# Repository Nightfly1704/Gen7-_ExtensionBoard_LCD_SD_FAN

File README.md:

Gen7-_ExtensionBoard_LCD_SD_FAN
==============================

Extension Board for Gen7 Electronics Version 1.4.1/1.5

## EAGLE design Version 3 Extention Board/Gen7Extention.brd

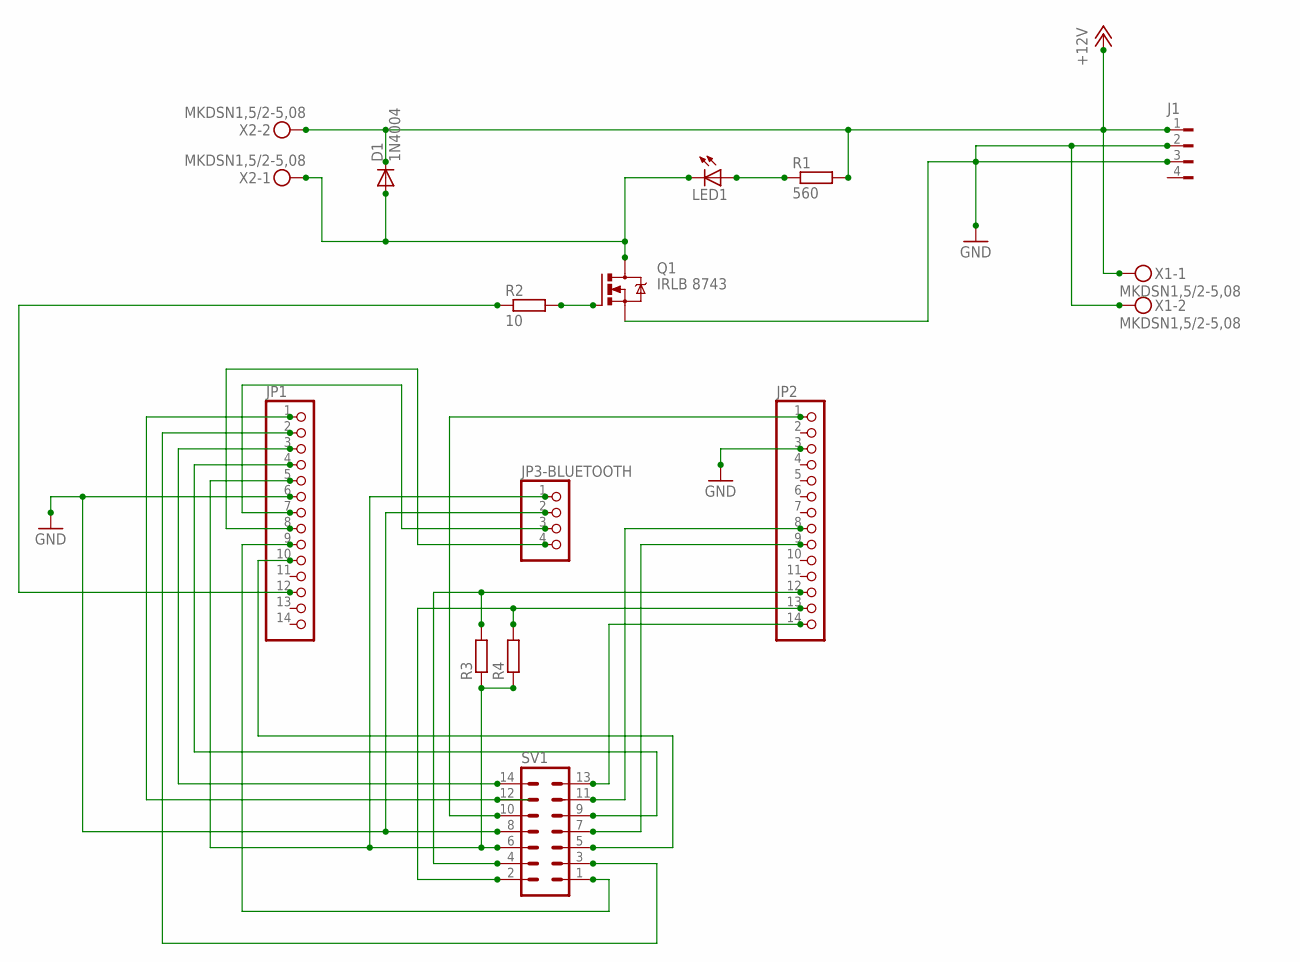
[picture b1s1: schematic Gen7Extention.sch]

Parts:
D1: 1N4004; DO41-10
J1: FLOPPY-4
JP1, JP2: PINHD-1X14; 1X14
JP3-BLUETOOTH: PINHD-1X4; 1X04
LED1: LED3MM
Q1: IRLB 8743; TO220BV
R1: 560; 0207/10
R2: 10; 0207/10
R3: R-EU_0207/5V; 0207/5V
R4: R-EU_0207/2V; 0207/2V
SV1: ML14
X1, X2: MKDSN1,5/2-5,08

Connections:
+12V: D1.C, J1.1, R1.2, X1.1, X2.2
GND: J1.2, J1.3, JP1.6, JP2.3, JP3-BLUETOOTH.2, Q1.S, SV1.8, X1.2
unnamed: JP1.1, SV1.12
unnamed: JP1.2, SV1.3
unnamed: JP1.3, SV1.14
unnamed: JP1.4, SV1.9
unnamed: JP1.5, JP3-BLUETOOTH.1, R3.1, R4.1, SV1.6
unnamed: JP1.7, JP3-BLUETOOTH.3
unnamed: JP1.8, JP3-BLUETOOTH.4
unnamed: D1.A, LED1.K (C), Q1.D, X2.1
unnamed: LED1.A, R1.1
unnamed: JP1.12, R2.1
unnamed: Q1.G, R2.2
unnamed: JP2.13, R4.2, SV1.2
unnamed: JP2.12, R3.2, SV1.4
unnamed: JP2.14, SV1.13
unnamed: JP2.1, SV1.10
unnamed: JP2.8, SV1.11
unnamed: JP2.9, SV1.7
unnamed: JP1.9, SV1.1
unnamed: JP1.10, SV1.5

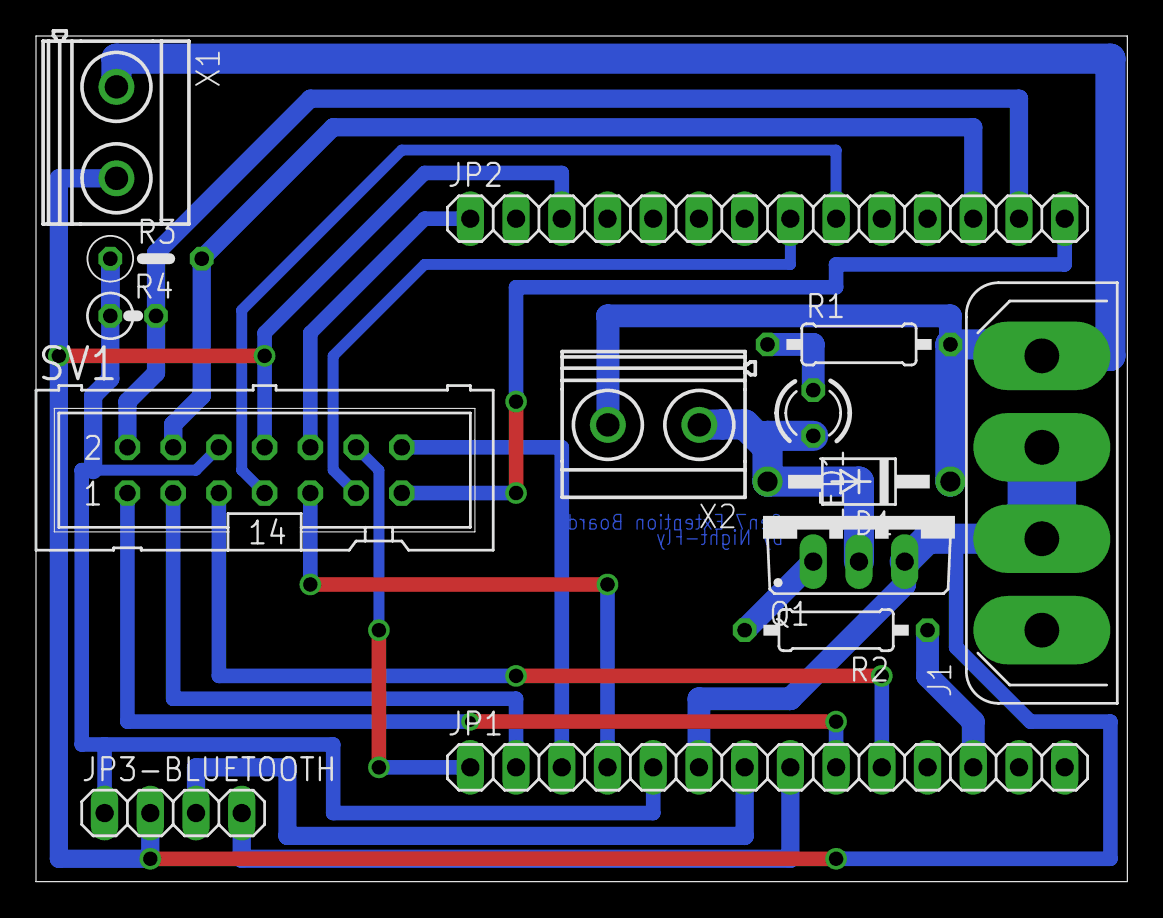
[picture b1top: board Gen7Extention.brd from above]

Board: 2 copper layers, 60.6 x 47.0 mm, 14 parts (0 on the bottom side), 21 nets.

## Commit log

2013-11-18 Update README.md
    Need more Coffee
2013-11-18 LCD-Board Housing
2013-11-18 Updated LCDBoard_Housing
    Printed parts separated
    Added 3D PDF for visualization
2014-01-23 Pin assignments
